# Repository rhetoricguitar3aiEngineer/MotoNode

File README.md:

# MotoNodeIQ

Motorcycle electronics for the 2003 Suzuki Katana 600: CAN body-electronics boards, an
ignition controller, and an Android telemetry app. Reorganized 2026-10-10. This repo mirrors the
`MotoNodeIQ` folder on the design PC, which is the source of truth for the current hardware.

**Status: designed and checked in software (KiCad 10 ERC/DRC clean), nothing built or bench-tested.**

| Folder | What | Status |
|---|---|---|
| [`Boards/`](Boards/) | **Front and rear CAN modules**: `front/`, `rear/` (Rev B, 76.2 x 50.8 mm) plus `generator/` that rebuilds them (`generator/build.py <board>`). `hub/` is superseded: the hub is now the ignition board (see below). [`Boards/README.md`](Boards/README.md) has the details and the "before you order" list. | Live (`hub/` superseded) |
| [`Boards/nodeiq_front_revG/`](Boards/nodeiq_front_revG/) | Hand-built Front Module Rev G, kept beside the generated `front/` | Reference |
| [`Ignition/RevE/`](Ignition/RevE/) | **The hub.** Ignition controller + hub on one board, Rev E: 4 TCI + 1 CDI, ESP32-S3, IMU/GPS/sensor inputs, 6-layer 100 x 70 mm, fully routed, DRC clean | Live |
| [`Telemetry/MotoNodeTelemetry/`](Telemetry/MotoNodeTelemetry/) | Android telemetry app + `esp32/` firmware (Gradle build output stripped; Android Studio regenerates it) | Live |
| [`Docs/`](Docs/) | Design brief, implementation plan, connector selection, source audit, board status (from the Codex NodeIQ work), plus [`OVERVIEW.md`](Docs/OVERVIEW.md) | Reference |
| [`Archive/`](Archive/) | Superseded material, see [`Archive/README.md`](Archive/README.md) | Archived |

`_Keys/keyMN1` (the Android app-signing keystore) lives beside these folders on the PC and is
**deliberately not in this repo**. It is irreplaceable: back it up off the PC, and never commit it.
`.gitignore` blocks `_Keys/` and keystore files.

## Not yet in the repo

Docs, BOMs, check reports and the telemetry source are here. The KiCad design files (`.kicad_*`,
libraries, `fab/`) and the Python generators (`Boards/generator/`, `Ignition/RevE/pcb_layout/`,
`Ignition/RevE/spice/`) still need to be pushed from the PC. See
[`Docs/FILES_TO_ADD.md`](Docs/FILES_TO_ADD.md).

## Google Drive

My Drive/**MotoNodeIQ** (<https://drive.google.com/drive/folders/14qOt1xsgB9vhRgdrsN2DCoWwWa2cDshs>)
holds what is *not* here: NodeIQ Android app releases (App/), ESP32 firmware (Firmware/), marketing
images/videos (Marketing/), reports, AI handoffs, and pre-Rev-B hardware (Archive/). "My Computer (1)"
on Drive is a stale backup of the old PC layout.

## Decided

- **Ignition is part of the hub** (2026-10-10). The Rev E ignition board is the system hub, so the
  system is Ignition/hub + Front + Rear. `Boards/hub/` is superseded and kept only as a source of
  circuits to port. See [`Docs/OVERVIEW.md`](Docs/OVERVIEW.md) §4 for the hub functions Rev E
  doesn't have yet.

## Tools

- KiCad 10.0.6. Its Python (`D:\Documents\bin\python.exe` on the PC) is needed by `pcbgen.py` / `pcbfinish.py`.
- Router and other generator scripts use system Python (numpy, scipy, shapely, PIL).
- ngspice 42 for `Ignition/RevE/spice/`.
- Android Studio (Gradle 9.5, JDK 17) and the Arduino ESP32 core for `Telemetry/`.

## Safety

The ignition board generates ~350 V on the CDI bus. Treat an assembled board as live and lethal, and
bench-test with current-limited supplies before it goes near a bike.

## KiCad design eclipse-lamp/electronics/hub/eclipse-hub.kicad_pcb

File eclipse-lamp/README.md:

# ECLIPSE Tree: a cedar elm made of light

ECLIPSE Tree is a desk lamp in the form of an old cedar elm (*Ulmus crassifolia*). In
daylight it reads as a small tree in leaf; switched on, it fills with light:

* **Grown, not drawn.** The crown is grown by space colonisation: buds compete for space in
  a rounded crown, so the wood forks where the space divides and tapers continuously (pipe
  model) from a 77 mm trunk through three leaders to **1,174 twigs**.
* **Leaves.** 40 flexible-circuit sprays carry **800 LED leaves** (0402) among **21,770
  leaves of light-diffusing film**, so the foliage glows green-gold around every light.
* **Trunk.** The trunk, its fork and its buttress roots are a thin bronze shell around a
  light-diffusing acrylic light-guide tube. Light travels down the tube and leaks out
  wherever the bark is split, so the trunk glows through its furrows.
* **Seeds.** End-glow optical fibres light **567 diffusing samaras** (cedar-elm seeds) among
  the twigs.

Warm and cool light is interleaved everywhere, so the whole tree can be mixed from candle
glow to daylight, dimmed to embers, or left with only its roots glowing.

| | |
|---|---|
|  |  |
|  |  |
|  |  |
|  |  |

## Four light paths, one driver per colour channel

```
                     ┌─ 2 top LEDs ──► fibre ferrule ──► 4 bundles × ~142 end-glow fibres ──► 567 glowing samaras
 HUB light engine  ──┤
 (in the trunk fork) └─ 2 bottom LEDs ─► trunk PMMA light-guide tube ──► TIR + extraction ──► glowing bark furrows
        │                                                                                    and buttress roots
        └─ then 10 LED sprigs in series ──► 20 × 0402 leaves each ──► 800 LED leaves ──► glowing leaf film

 CORE board (base): USB-C PD 9 V → 4 × TPS61165 constant-current boost @ 100 mA (W1 C1 W2 C2)
                    ATtiny1616 touch wheel, colour mix, + 8 LEDs → opal root-glow band (night light)
```

Each colour channel is **one series string of 11 elements** (≈31.5 V, inside the 38 V OVP):
first the hub's 4-LED light-engine group, then 10 sprigs. So all four optical systems dim
and colour-shift together from the same four drivers. The core board circuit is unchanged
from the previous revision, and only 10 wires run down the trunk.

## Key specs

| | |
|---|---|
| Size | ≈435 mm tall, crown ≈370 × 360 mm, on a Ø150 mm base |
| Tree | Space-colonisation grown cedar elm: 77 mm trunk (cast bronze shell + PMMA light-guide tube), 7 buttress roots, 3 leaders, 1,174 branches and twigs, 21,770 film leaves (seeded, reproducible) |
| Light sources | 800 × 0402 LED leaves + 16 × 2835 light-engine LEDs (8 → fibres, 8 → trunk core) + 8 × 2835 root glow |
| Optics | PMMA light-guide trunk with fissure extraction · light-diffusing leaf film lit by the LED leaves · 567 × 0.5 mm end-glow PMMA fibres in 4 bundles · 567 diffusing-epoxy samaras · opal root band |
| Light | 12.6 W max LED power (firmware cap ≈8.5 W), ≈600 lm total (estimated), 2700-6500 K, flicker-free |
| Mass / stability | ≈4.1 kg, centre of gravity 8.5 mm from the base centre (66 mm inside the base edge) |
| Power / controls | USB-C PD 9 V (18 W+ charger), capacitive wheel through 3 mm glass |

## What's in this folder

```
eclipse-lamp/
├── mechanical/   tree_gen.py (space-colonisation cedar elm: trunk, fork, roots, wood, sprigs, samaras, foliage),
│                 eclipse_cad.py (CadQuery, mass/CoG), wiring_map.py, out/ (STEP/STL, big STEPs zipped,
│                 foliage.stl leaf-cutting file, parts.json)
├── electronics/
│   ├── core/     KiCad 9: base board (power, 4 drivers, touch MCU, root glow), unchanged circuit
│   ├── hub/      KiCad 9: Ø56 two-sided light engine in the trunk fork (16 LEDs) + 40 sprig lands + chaining + NTC
│   ├── sprig/    KiCad 9: polyimide flex cedar-elm spray, 20 × 0402 LED leaves (×40 per lamp)
│   ├── lib/      custom footprints + 3D models
│   └── tools/    generators: schematics (wire router), PCBs, layouts, netlist checks, fab export
├── bom/          eclipse_bom.csv, BOM.md (≈$147 material at 1k units, estimates)
├── renders/      Cycles renders + KiCad board renders, render_blender.py
└── docs/         DESIGN.md (design notes, optics, calculations), WIRING.md (sprig map)
```

## Verification

Every schematic draws every signal connection as a visible wire. There are no net labels,
and power uses power symbols only (see `/CLAUDE.md`).

| Check | Core | Hub | Sprig |
|---|---|---|---|
| ERC | 0 / 0 | 0 / 0 | 0 / 0 |
| DRC | 0 violations | 0 violations | 0 violations |
| Unrouted | 0 | 0 | 0 |
| Schematic ↔ PCB parity | 0 issues | 0 issues | 0 issues |
| Netlist vs design intent | 0 mismatches | 0 mismatches | 0 mismatches |

## Rebuild everything

Requires KiCad 9 (`kicad-cli` + `pcbnew` Python), CadQuery 2.x, numpy, scipy, shapely, Freerouting 1.9
(core board only, Java 21 + `xvfb-run`) and the `bpy` 5.x module for renders.

```sh
cd electronics/tools
python3 make_footprints.py && python3 make_3d_models.py
for b in core hub sprig; do
  python3 design_$b.py ../$b/eclipse-$b.kicad_sch
  (cd ../$b && kicad-cli sch export netlist --format kicadsexpr -o eclipse-$b.net eclipse-$b.kicad_sch)
  python3 verify_netlist.py design_$b ../$b/eclipse-$b.net
done
python3 pcb_hub.py && python3 pcb_sprig.py   # parametric layouts
./route_core.sh                             # core: placement → Freerouting → pours → DRC
./export_fab.sh                             # gerbers, drill, P&P, PDFs, STEP/GLB, reports
cd ../../mechanical && python3 eclipse_cad.py && python3 wiring_map.py
cd ../bom && python3 make_bom.py
cd ../renders && python3 render_blender.py hero   # hero | trunk | leaves | night | studio | cool | detail
```

See [docs/DESIGN.md](docs/DESIGN.md) for the optics, the calculations and the open items.

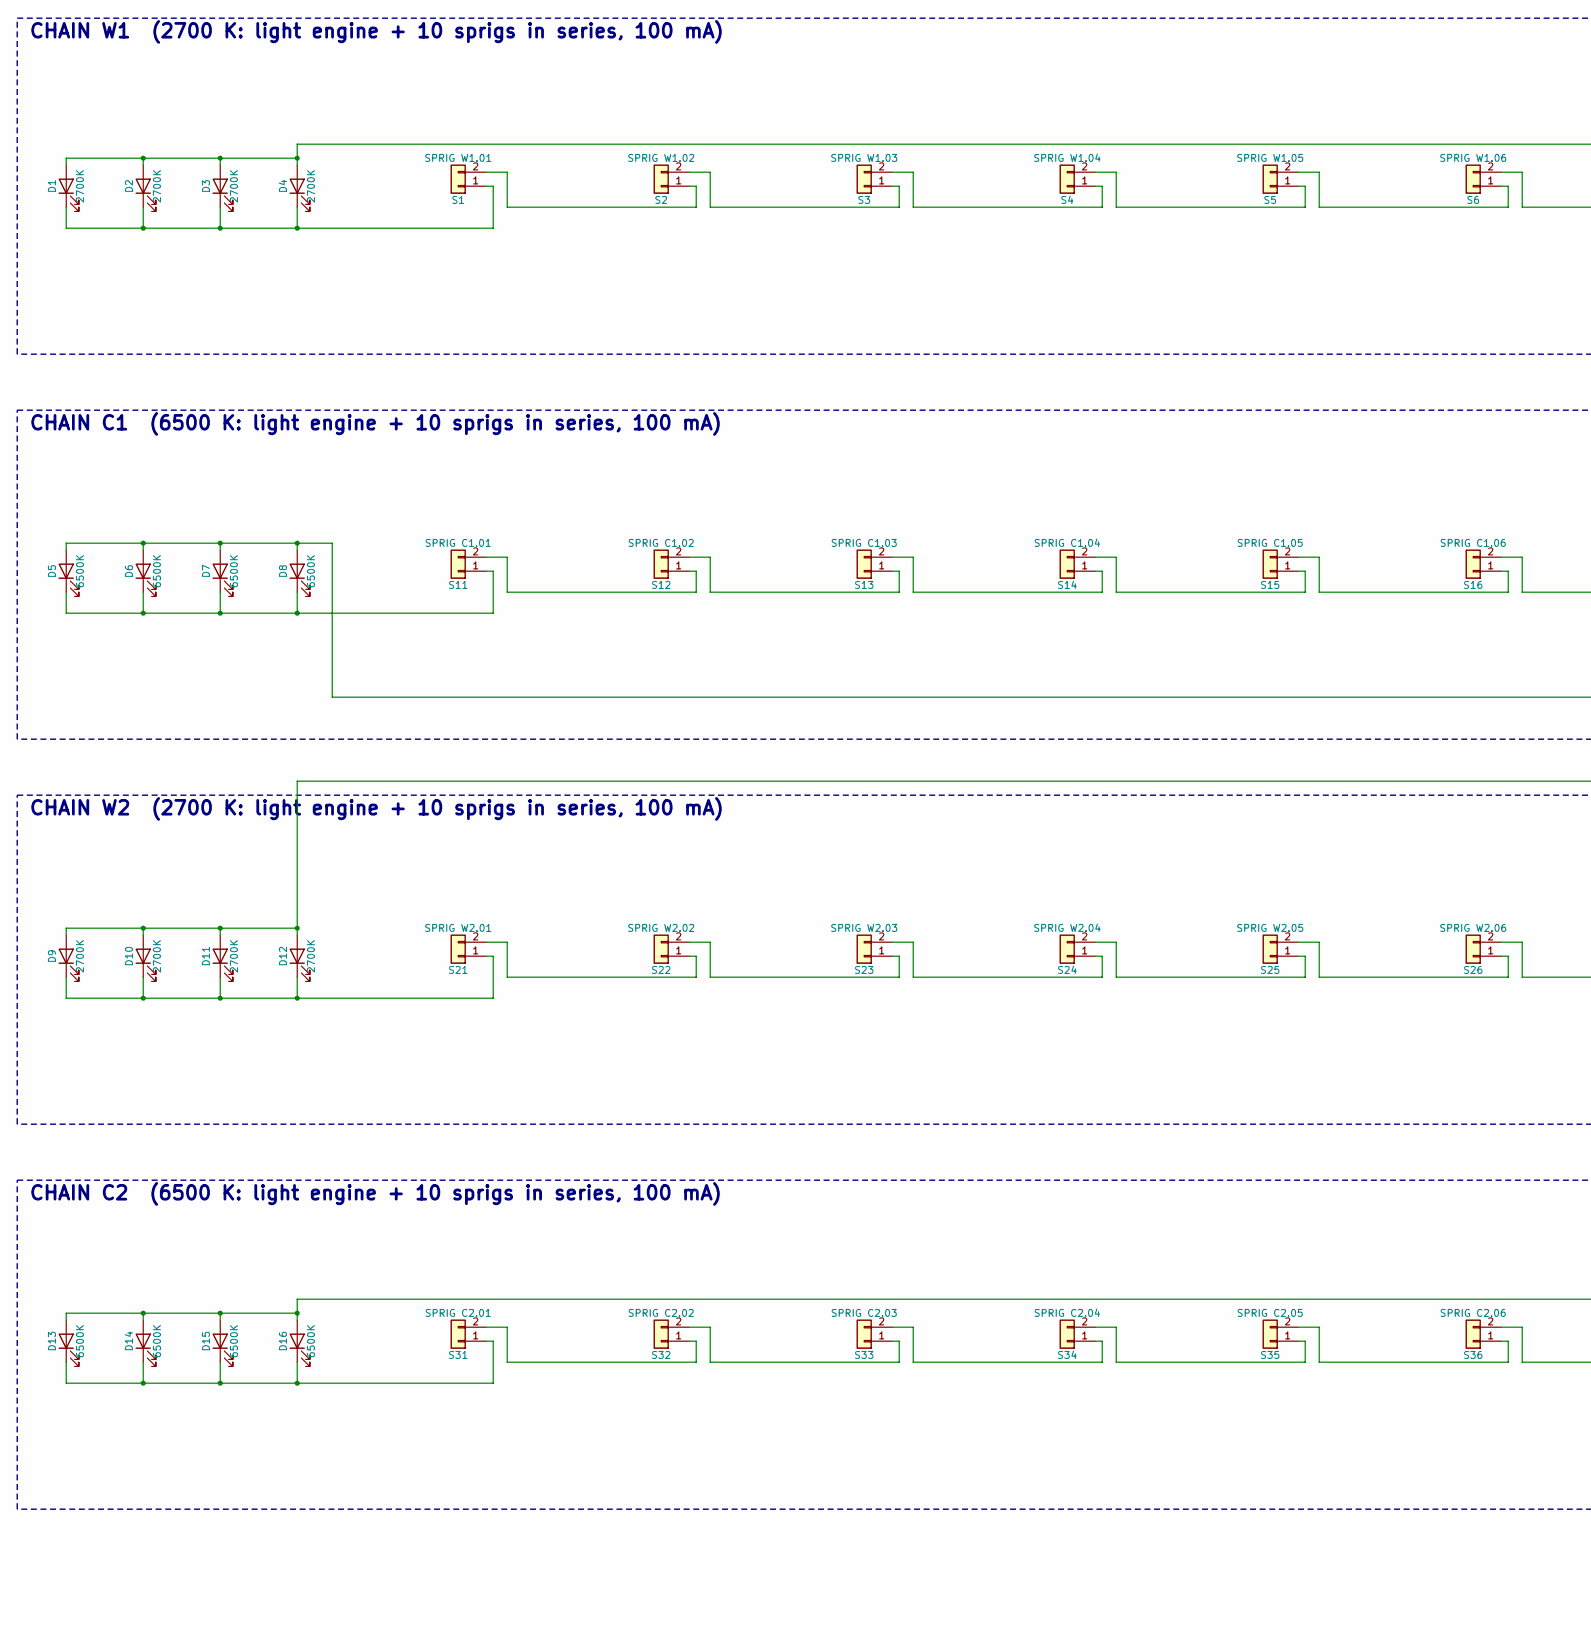
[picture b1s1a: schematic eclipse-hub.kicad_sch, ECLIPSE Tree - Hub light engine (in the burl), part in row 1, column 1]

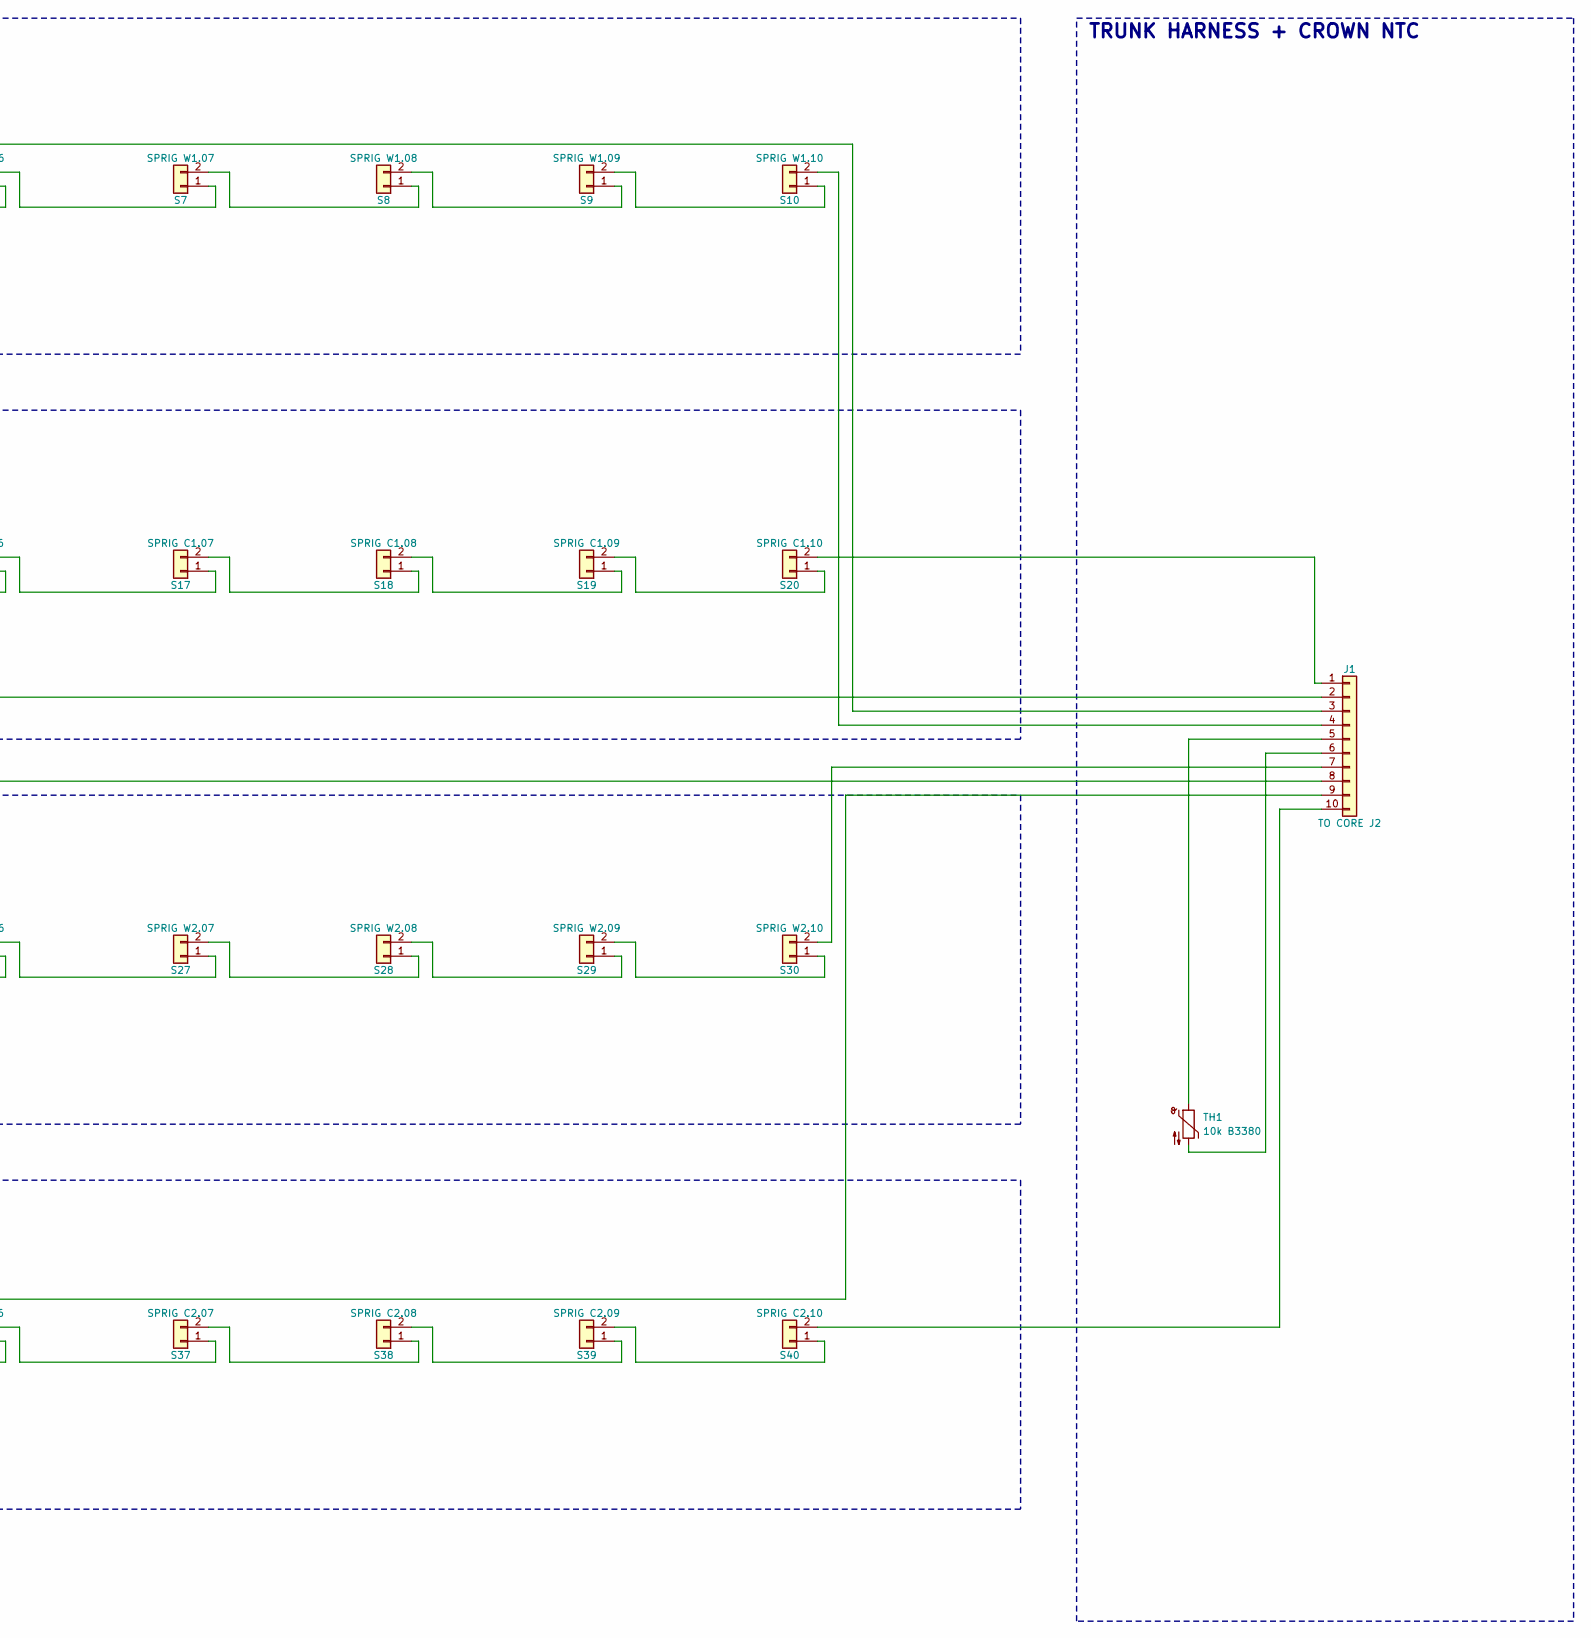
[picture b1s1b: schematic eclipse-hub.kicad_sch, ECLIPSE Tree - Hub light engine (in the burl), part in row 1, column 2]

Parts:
D1, D2, D3, D4, D9, D10, D11, D12: 2700K; LED_PLCC_2835; MPN LM281B+ 2700K
D5, D6, D7, D8, D13, D14, D15, D16: 6500K; LED_PLCC_2835; MPN LM281B+ 6500K
J1: TO CORE J2; HubTrunkPads; MPN wire lands
S1: SPRIG W1.01; HubSprigPads; MPN wire lands
S2: SPRIG W1.02; HubSprigPads; MPN wire lands
S3: SPRIG W1.03; HubSprigPads; MPN wire lands
S4: SPRIG W1.04; HubSprigPads; MPN wire lands
S5: SPRIG W1.05; HubSprigPads; MPN wire lands
S6: SPRIG W1.06; HubSprigPads; MPN wire lands
S7: SPRIG W1.07; HubSprigPads; MPN wire lands
S8: SPRIG W1.08; HubSprigPads; MPN wire lands
S9: SPRIG W1.09; HubSprigPads; MPN wire lands
S10: SPRIG W1.10; HubSprigPads; MPN wire lands
S11: SPRIG C1.01; HubSprigPads; MPN wire lands
S12: SPRIG C1.02; HubSprigPads; MPN wire lands
S13: SPRIG C1.03; HubSprigPads; MPN wire lands
S14: SPRIG C1.04; HubSprigPads; MPN wire lands
S15: SPRIG C1.05; HubSprigPads; MPN wire lands
S16: SPRIG C1.06; HubSprigPads; MPN wire lands
S17: SPRIG C1.07; HubSprigPads; MPN wire lands
S18: SPRIG C1.08; HubSprigPads; MPN wire lands
S19: SPRIG C1.09; HubSprigPads; MPN wire lands
S20: SPRIG C1.10; HubSprigPads; MPN wire lands
S21: SPRIG W2.01; HubSprigPads; MPN wire lands
S22: SPRIG W2.02; HubSprigPads; MPN wire lands
S23: SPRIG W2.03; HubSprigPads; MPN wire lands
S24: SPRIG W2.04; HubSprigPads; MPN wire lands
S25: SPRIG W2.05; HubSprigPads; MPN wire lands
S26: SPRIG W2.06; HubSprigPads; MPN wire lands
S27: SPRIG W2.07; HubSprigPads; MPN wire lands
S28: SPRIG W2.08; HubSprigPads; MPN wire lands
S29: SPRIG W2.09; HubSprigPads; MPN wire lands
S30: SPRIG W2.10; HubSprigPads; MPN wire lands
S31: SPRIG C2.01; HubSprigPads; MPN wire lands
S32: SPRIG C2.02; HubSprigPads; MPN wire lands
S33: SPRIG C2.03; HubSprigPads; MPN wire lands
S34: SPRIG C2.04; HubSprigPads; MPN wire lands
S35: SPRIG C2.05; HubSprigPads; MPN wire lands
S36: SPRIG C2.06; HubSprigPads; MPN wire lands
S37: SPRIG C2.07; HubSprigPads; MPN wire lands
S38: SPRIG C2.08; HubSprigPads; MPN wire lands
S39: SPRIG C2.09; HubSprigPads; MPN wire lands
S40: SPRIG C2.10; HubSprigPads; MPN wire lands
TH1: 10k B3380; R_0603_1608Metric; MPN NCP18XH103F03RB

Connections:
unnamed: D1.2 (A), D2.2 (A), D3.2 (A), D4.2 (A), J1.3
unnamed: D1.1 (K), D2.1 (K), D3.1 (K), D4.1 (K), S1.1
unnamed: D5.2 (A), D6.2 (A), D7.2 (A), D8.2 (A), J1.2
unnamed: D5.1 (K), D6.1 (K), D7.1 (K), D8.1 (K), S11.1
unnamed: D9.2 (A), D10.2 (A), D11.2 (A), D12.2 (A), J1.8
unnamed: D9.1 (K), D10.1 (K), D11.1 (K), D12.1 (K), S21.1
unnamed: D13.2 (A), D14.2 (A), D15.2 (A), D16.2 (A), J1.9
unnamed: D13.1 (K), D14.1 (K), D15.1 (K), D16.1 (K), S31.1
unnamed: J1.1, S20.2
unnamed: J1.4, S10.2
unnamed: J1.5, TH1.1
unnamed: J1.6, TH1.2
unnamed: J1.7, S30.2
unnamed: J1.10, S40.2
unnamed: S1.2, S2.1
unnamed: S2.2, S3.1
unnamed: S3.2, S4.1
unnamed: S4.2, S5.1
unnamed: S5.2, S6.1
unnamed: S6.2, S7.1
unnamed: S7.2, S8.1
unnamed: S8.2, S9.1
unnamed: S9.2, S10.1
unnamed: S11.2, S12.1
unnamed: S12.2, S13.1
unnamed: S13.2, S14.1
unnamed: S14.2, S15.1
unnamed: S15.2, S16.1
unnamed: S16.2, S17.1
unnamed: S17.2, S18.1
unnamed: S18.2, S19.1
unnamed: S19.2, S20.1
unnamed: S21.2, S22.1
unnamed: S22.2, S23.1
unnamed: S23.2, S24.1
unnamed: S24.2, S25.1
unnamed: S25.2, S26.1
unnamed: S26.2, S27.1
unnamed: S27.2, S28.1
unnamed: S28.2, S29.1
unnamed: S29.2, S30.1
unnamed: S31.2, S32.1
unnamed: S32.2, S33.1
unnamed: S33.2, S34.1
unnamed: S34.2, S35.1
unnamed: S35.2, S36.1
unnamed: S36.2, S37.1
unnamed: S37.2, S38.1
unnamed: S38.2, S39.1
unnamed: S39.2, S40.1

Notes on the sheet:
CHAIN W1 (2700 K: light engine + 10 sprigs in series, 100 mA)
CHAIN C1 (6500 K: light engine + 10 sprigs in series, 100 mA)
CHAIN W2 (2700 K: light engine + 10 sprigs in series, 100 mA)
CHAIN C2 (6500 K: light engine + 10 sprigs in series, 100 mA)
TRUNK HARNESS + CROWN NTC

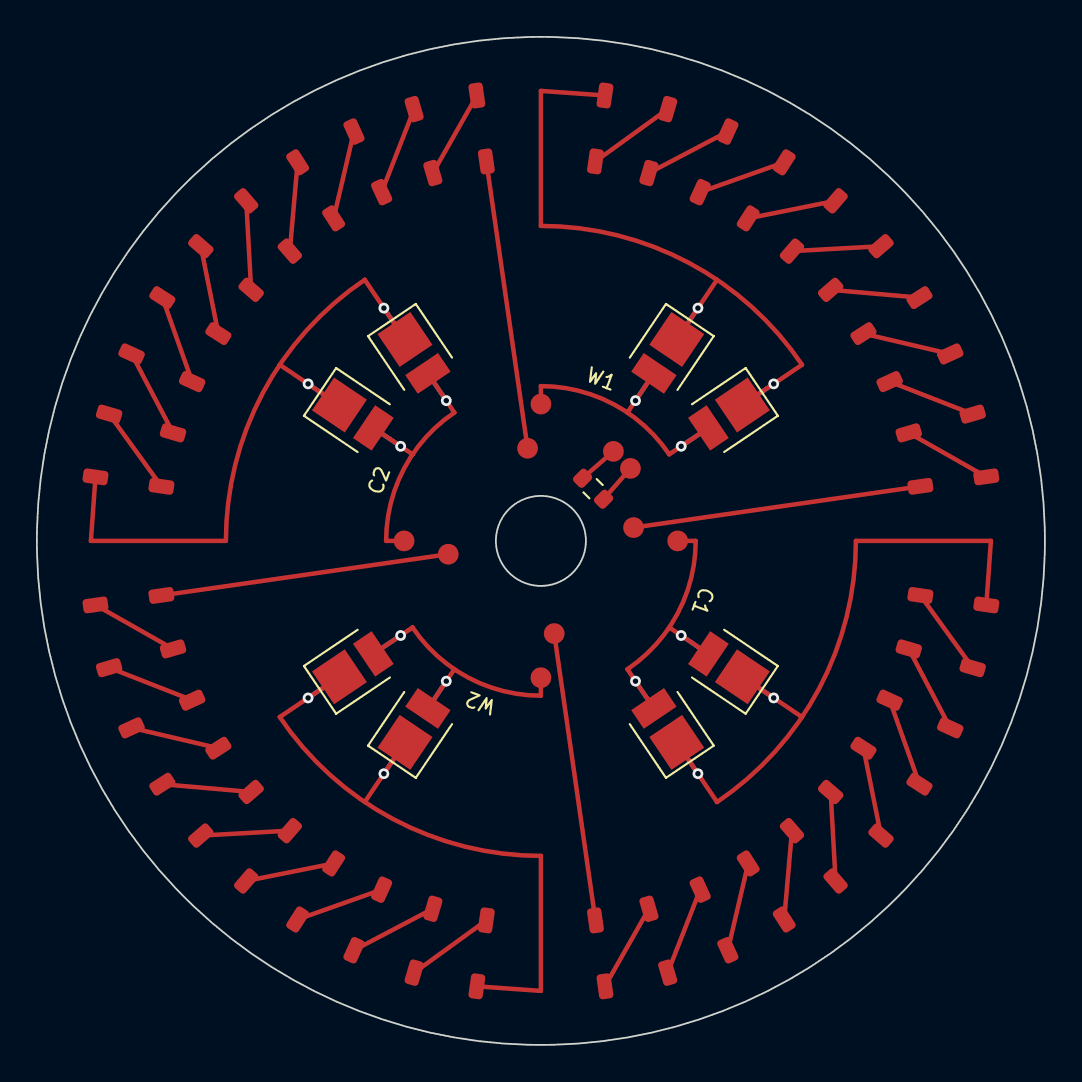
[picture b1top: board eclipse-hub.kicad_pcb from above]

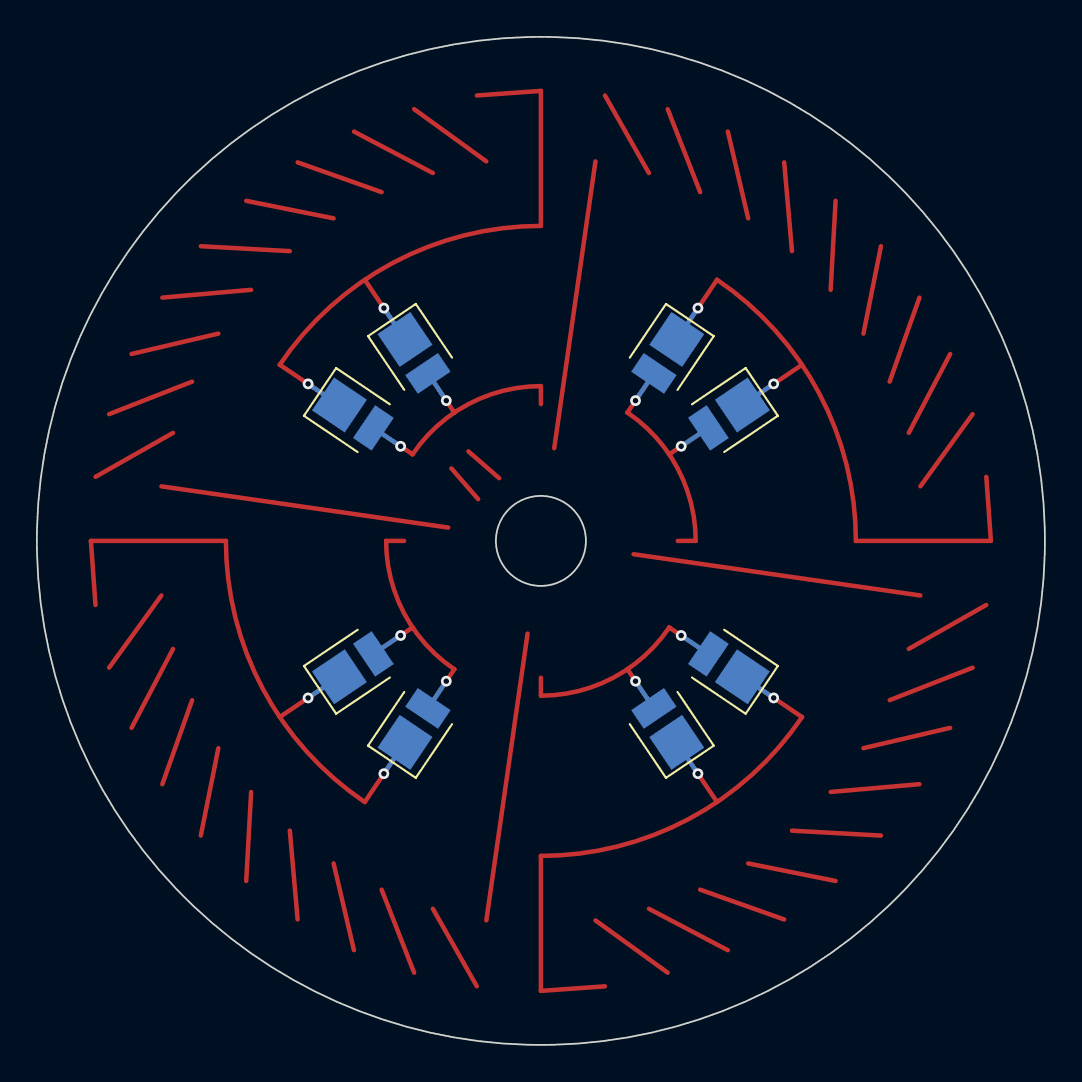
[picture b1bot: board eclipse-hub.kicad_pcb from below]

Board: 2 copper layers, 56.0 x 56.0 mm, 58 parts (8 on the bottom side), 50 nets.

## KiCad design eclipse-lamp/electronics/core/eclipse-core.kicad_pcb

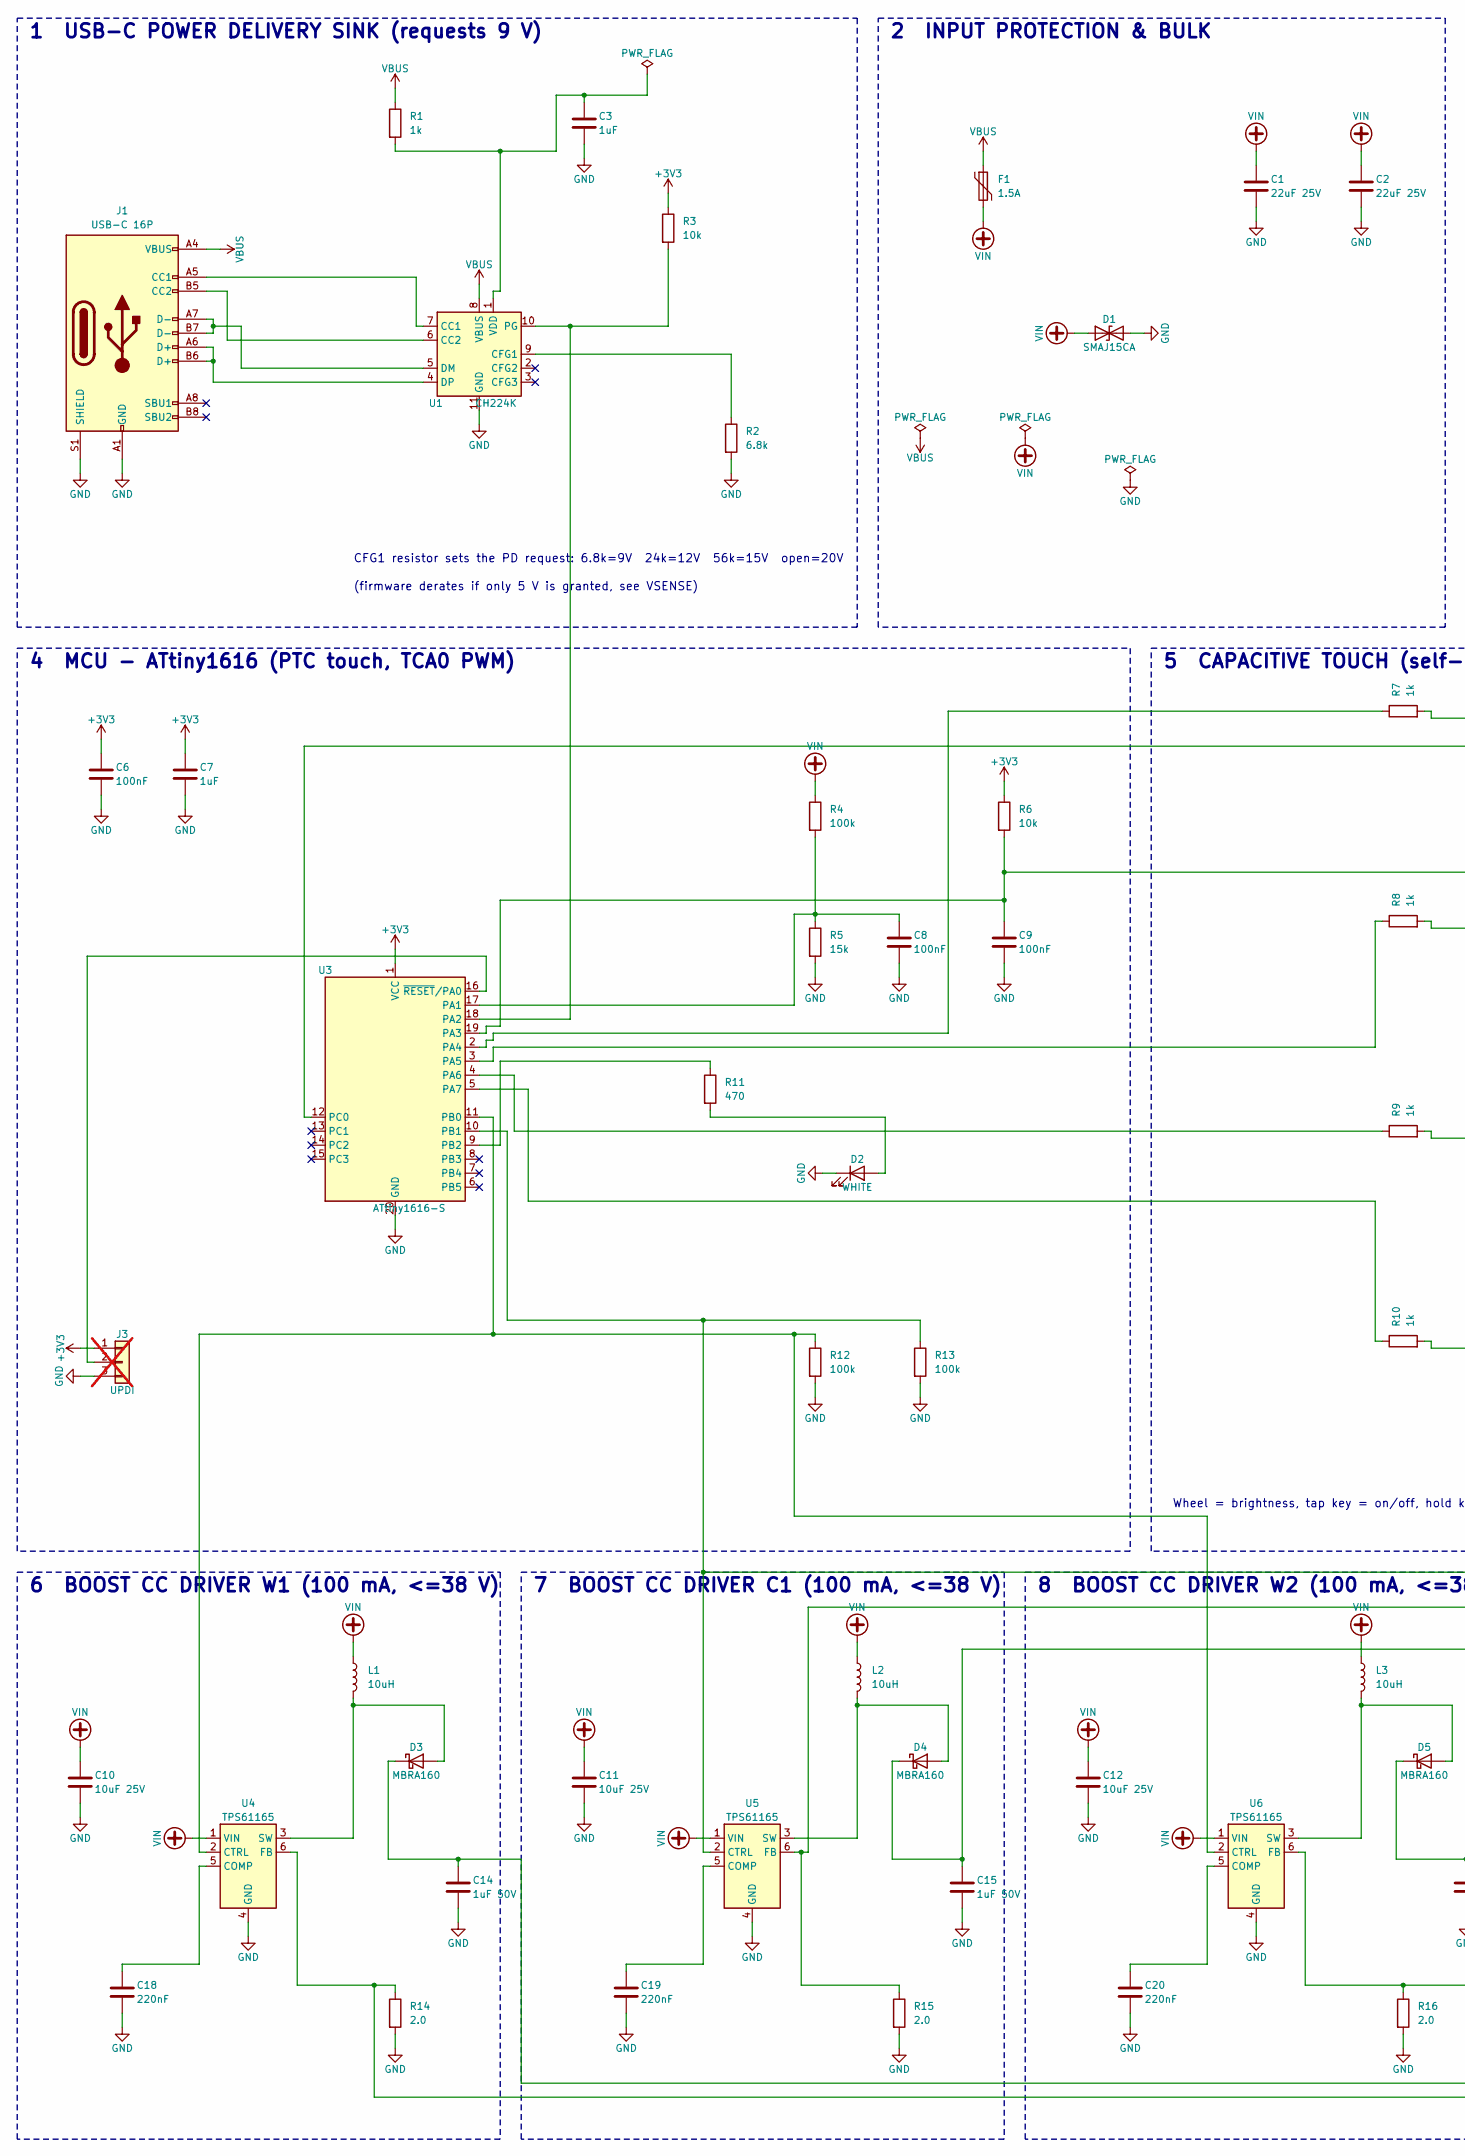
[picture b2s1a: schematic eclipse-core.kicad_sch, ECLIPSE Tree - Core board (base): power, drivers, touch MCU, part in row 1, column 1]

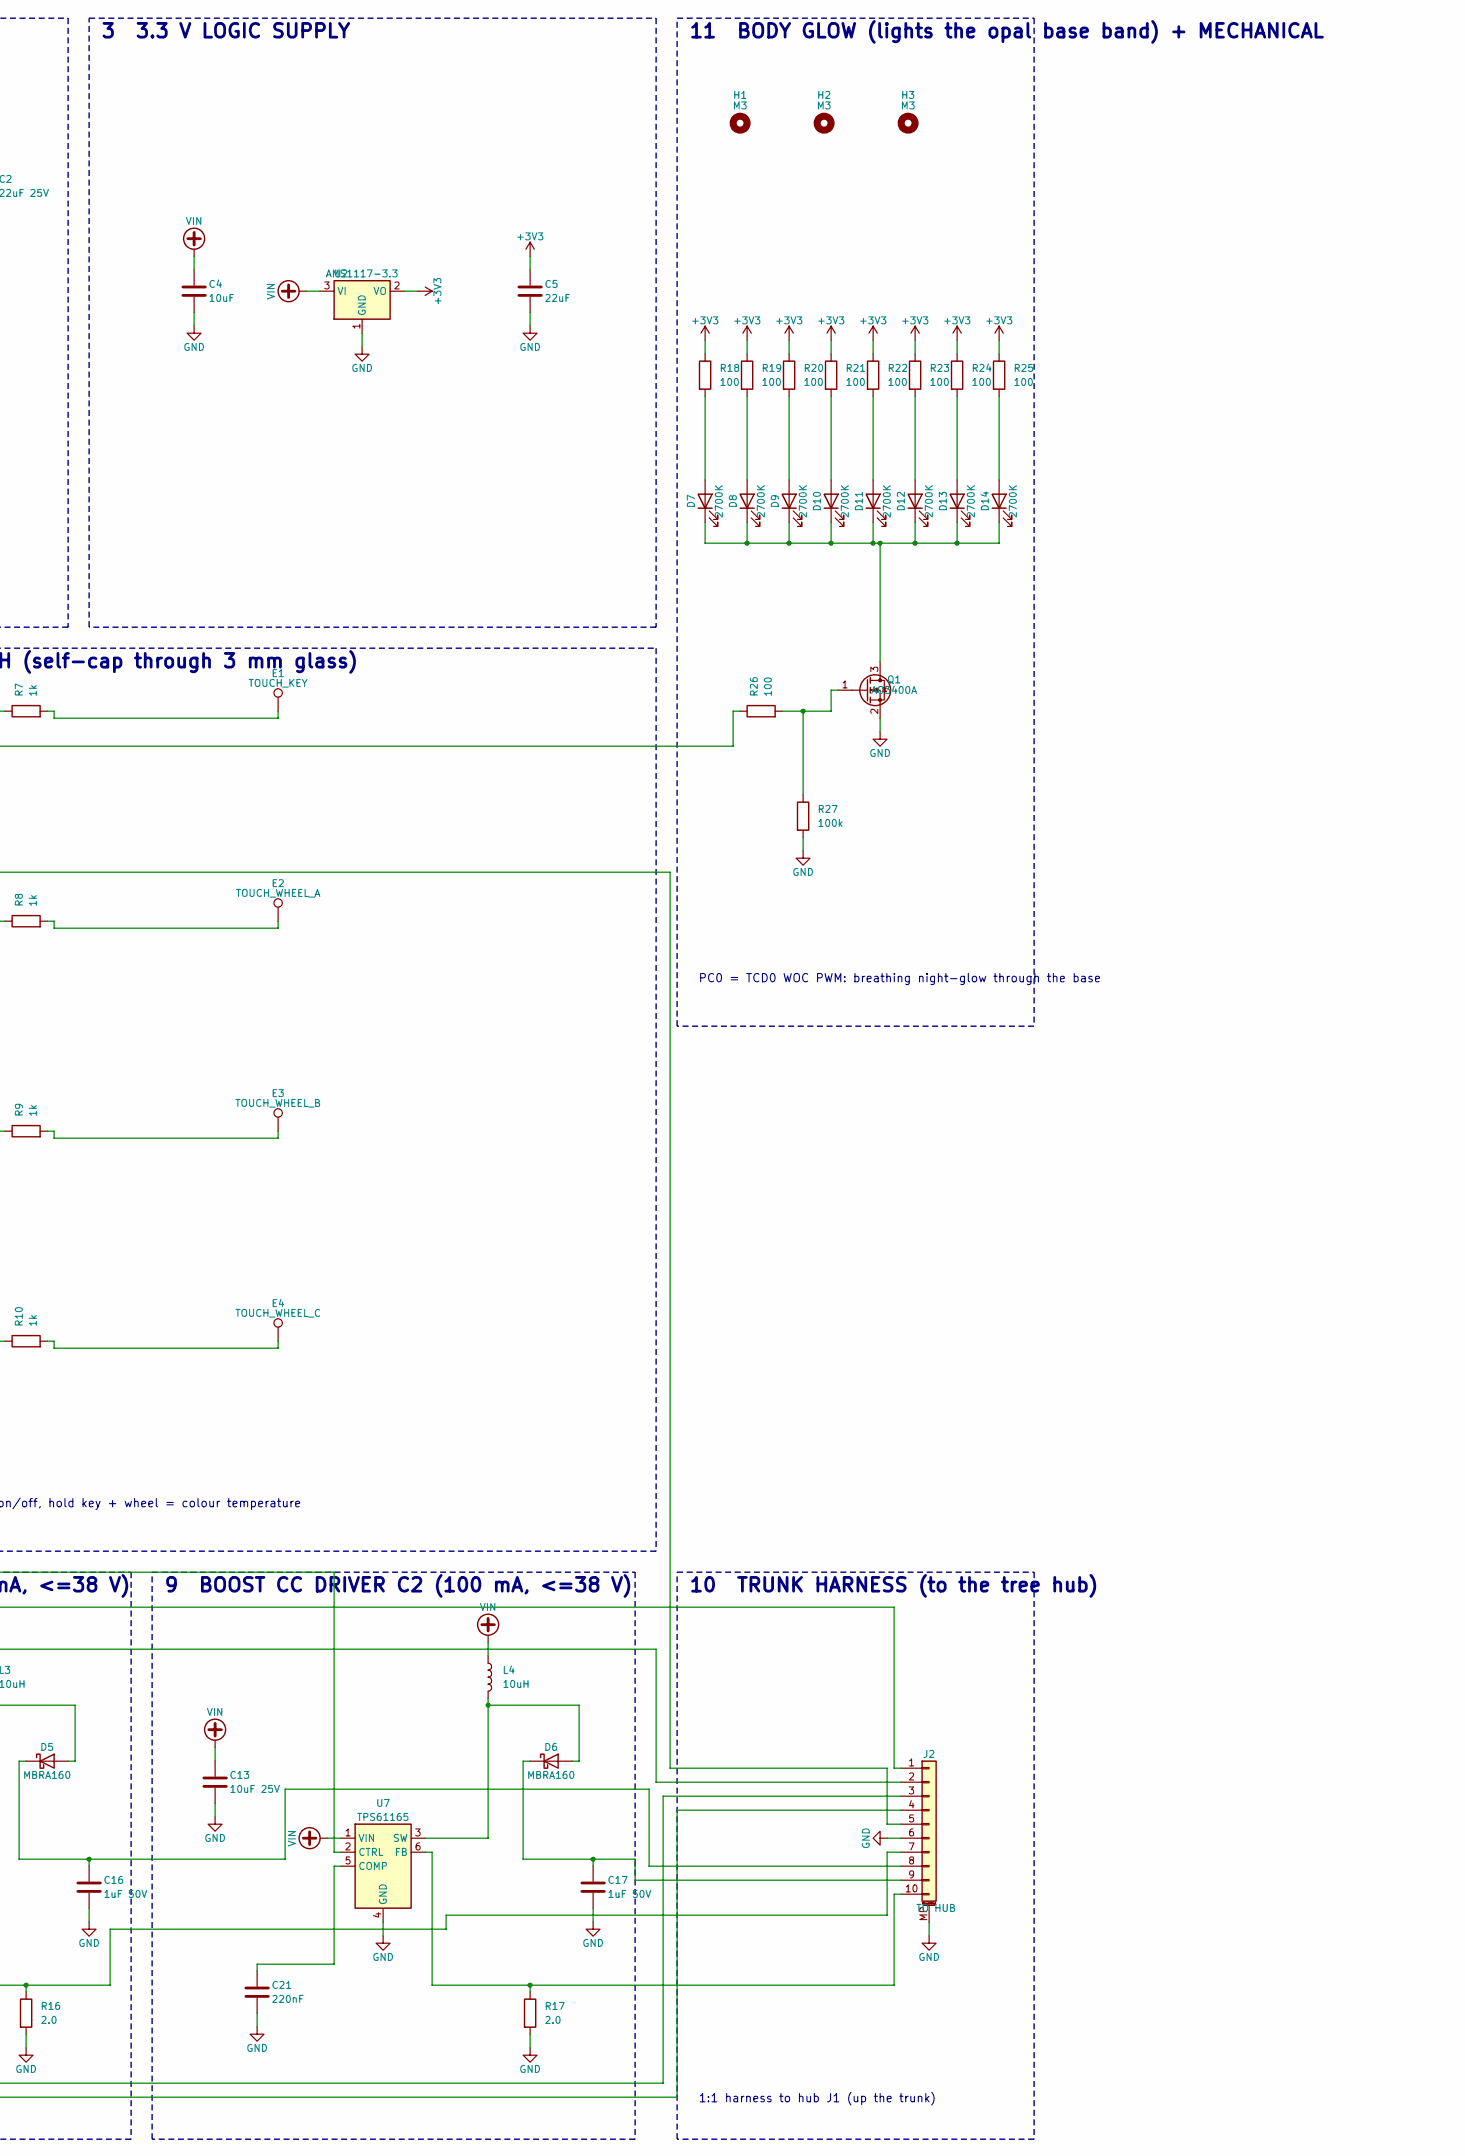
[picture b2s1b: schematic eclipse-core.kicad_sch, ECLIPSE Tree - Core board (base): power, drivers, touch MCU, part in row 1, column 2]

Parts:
C1, C2: 22uF 25V; C_1206_3216Metric; MPN GRM31CR61E226KE15L
C3, C7: 1uF; C_0603_1608Metric; MPN GRM188R61E105KA12D
C4: 10uF; C_0805_2012Metric; MPN CL21A106KAYNNNE
C5: 22uF; C_0805_2012Metric; MPN CL21A226MAQNNNE
C6, C8, C9: 100nF; C_0603_1608Metric; MPN GRM188R71H104KA93D
C10, C11, C12, C13: 10uF 25V; C_0805_2012Metric; MPN CL21A106KAYNNNE
C14, C15, C16, C17: 1uF 50V; C_1206_3216Metric; MPN GRM31MR71H105KA88L
C18, C19, C20, C21: 220nF; C_0603_1608Metric; MPN GRM188R71E224KA88D
D1: SMAJ15CA; D_SMA; MPN SMAJ15CA
D2: WHITE; LED_0603_1608Metric; MPN LTW-C191TS5
D3, D4, D5, D6: MBRA160; D_SMA; MPN MBRA160T3G
D7, D8, D9, D10, D11, D12, D13, D14: 2700K; LED_PLCC_2835; MPN LM281B+ 2700K
E1: TOUCH_KEY; TouchKey_D14; MPN PCB copper electrode
E2: TOUCH_WHEEL_A; TouchWheel_Seg120; MPN PCB copper electrode
E3: TOUCH_WHEEL_B; TouchWheel_Seg120; MPN PCB copper electrode
E4: TOUCH_WHEEL_C; TouchWheel_Seg120; MPN PCB copper electrode
F1: 1.5A; Fuse_1812_4532Metric; MPN MF-MSMF150/24X-2
H1, H2, H3: M3; MountingHole_3.2mm_M3
J1: USB-C 16P; USB_C_Receptacle_HRO_TYPE-C-31-M-12; MPN TYPE-C-31-M-12; LCSC C165948
J2: TO HUB; JST_PH_S10B-PH-SM4-TB_1x10-1MP_P2.00mm_Horizontal; MPN S10B-PH-SM4-TB
J3: UPDI; PinHeader_1x03_P2.54mm_Vertical; MPN DNP (pogo pads); not fitted
L1, L2, L3, L4: 10uH; L_Bourns-SRN4018; MPN SRN4018-100M
Q1: AO3400A; SOT-23; MPN AO3400A
R1, R7, R8, R9, R10: 1k; R_0603_1608Metric; MPN RC0603FR-071KL
R2: 6.8k; R_0603_1608Metric; MPN RC0603FR-076K8L
R3, R6: 10k; R_0603_1608Metric; MPN RC0603FR-0710KL
R4, R12, R13, R27: 100k; R_0603_1608Metric; MPN RC0603FR-07100KL
R5: 15k; R_0603_1608Metric; MPN RC0603FR-0715KL
R11: 470; R_0603_1608Metric; MPN RC0603FR-07470RL
R14, R15, R16, R17: 2.0; R_0805_2012Metric; MPN RC0805FR-072RL
R18, R19, R20, R21, R22, R23, R24, R25, R26: 100; R_0603_1608Metric; MPN RC0603FR-07100RL
U1: CH224K; SSOP-10-1EP_3.9x4.9mm_P1mm_EP2.1x3.3mm; MPN CH224K; LCSC C970725
U2: AMS1117-3.3; SOT-223-3_TabPin2; MPN AMS1117-3.3; LCSC C6186
U3: ATtiny1616-S; SOIC-20W_7.5x12.8mm_P1.27mm; MPN ATTINY1616-SNR
U4, U5, U6, U7: TPS61165; SOT-23-6; MPN TPS61165DBVR

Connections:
+3V3: C5.1, C6.1, C7.1, J3.1, R3.1, R6.1, R18.1, R19.1, R20.1, R21.1, R22.1, R23.1, R24.1, R25.1, U2.2 (VO), U3.1 (VCC)
GND: C1.2, C2.2, C3.2, C4.2, C5.2, C6.2, C7.2, C8.2, C9.2, C10.2, C11.2, C12.2, C13.2, C14.2, C15.2, C16.2, C17.2, C18.2, C19.2, C20.2, C21.2, D1.2 (A2), D2.1 (K), J1.A1 (GND), J1.A12 (GND), J1.B1 (GND), J1.B12 (GND), J1.S1 (SHIELD), J2.6, J2.MP (MountPin), J3.3, Q1.2 (S), R2.2, R5.2, R12.2, R13.2, R14.2, R15.2, R16.2, R17.2, R27.2, U1.11 (GND), U2.1 (GND), U3.20 (GND), U4.4 (GND), U5.4 (GND), U6.4 (GND), U7.4 (GND)
unnamed: D2.2 (A), R11.2
unnamed: D3.2 (A), L1.2, U4.3 (SW)
unnamed: C14.1, D3.1 (K), J2.3
unnamed: D4.2 (A), L2.2, U5.3 (SW)
unnamed: C15.1, D4.1 (K), J2.2
unnamed: D5.2 (A), L3.2, U6.3 (SW)
unnamed: C16.1, D5.1 (K), J2.8
unnamed: D6.2 (A), L4.2, U7.3 (SW)
unnamed: C17.1, D6.1 (K), J2.9
unnamed: D7.2 (A), R18.2
unnamed: D8.2 (A), R19.2
unnamed: D9.2 (A), R20.2
unnamed: D10.2 (A), R21.2
unnamed: D7.1 (K), D8.1 (K), D9.1 (K), D10.1 (K), D11.1 (K), D12.1 (K), D13.1 (K), D14.1 (K), Q1.3 (D)
unnamed: D11.2 (A), R22.2
unnamed: D12.2 (A), R23.2
unnamed: D13.2 (A), R24.2
unnamed: D14.2 (A), R25.2
unnamed: E1.1, R7.2
unnamed: E2.1, R8.2
unnamed: E3.1, R9.2
unnamed: E4.1, R10.2
unnamed: J1.A5 (CC1), U1.7 (CC1)
unnamed: J1.B5 (CC2), U1.6 (CC2)
unnamed: J2.1, R15.1, U5.6 (FB)
unnamed: J2.4, R14.1, U4.6 (FB)
unnamed: C9.1, J2.5, R6.2, U3.19 (PA3)
unnamed: J2.7, R16.1, U6.6 (FB)
unnamed: J2.10, R17.1, U7.6 (FB)
unnamed: J3.2, U3.16 (~RESET/PA0)
unnamed: Q1.1 (G), R26.2, R27.1
unnamed: R2.1, U1.9 (CFG1)
unnamed: J1.A7 (D-), J1.B7 (D-), U1.5 (DM)
unnamed: J1.A6 (D+), J1.B6 (D+), U1.4 (DP)
unnamed: R3.2, U1.10 (PG), U3.18 (PA2)
unnamed: C3.1, R1.2, U1.1 (VDD)
unnamed: C8.1, R4.2, R5.1, U3.17 (PA1)
unnamed: R7.1, U3.2 (PA4)
unnamed: R8.1, U3.3 (PA5)
unnamed: R9.1, U3.4 (PA6)
unnamed: R10.1, U3.5 (PA7)
unnamed: R12.1, U3.11 (PB0), U4.2 (CTRL), U6.2 (CTRL)
unnamed: R13.1, U3.10 (PB1), U5.2 (CTRL), U7.2 (CTRL)
unnamed: R11.1, U3.9 (PB2)
unnamed: R26.1, U3.12 (PC0)
unnamed: C18.1, U4.5 (COMP)
unnamed: C19.1, U5.5 (COMP)
unnamed: C20.1, U6.5 (COMP)
unnamed: C21.1, U7.5 (COMP)
VBUS: F1.1, J1.A4 (VBUS), J1.A9 (VBUS), J1.B4 (VBUS), J1.B9 (VBUS), R1.1, U1.8 (VBUS)
VIN: C1.1, C2.1, C4.1, C10.1, C11.1, C12.1, C13.1, D1.1 (A1), F1.2, L1.1, L2.1, L3.1, L4.1, R4.1, U2.3 (VI), U4.1 (VIN), U5.1 (VIN), U6.1 (VIN), U7.1 (VIN)

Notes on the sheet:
1 USB-C POWER DELIVERY SINK (requests 9 V)
CFG1 resistor sets the PD request: 6.8k=9V 24k=12V 56k=15V open=20V
(firmware derates if only 5 V is granted, see VSENSE)
2 INPUT PROTECTION & BULK
3 3.3 V LOGIC SUPPLY
4 MCU - ATtiny1616 (PTC touch, TCA0 PWM)
5 CAPACITIVE TOUCH (self-cap through 3 mm glass)
Wheel = brightness, tap key = on/off, hold key + wheel = colour temperature
6 BOOST CC DRIVER W1 (100 mA, <=38 V)
7 BOOST CC DRIVER C1 (100 mA, <=38 V)
8 BOOST CC DRIVER W2 (100 mA, <=38 V)
9 BOOST CC DRIVER C2 (100 mA, <=38 V)
11 BODY GLOW (lights the opal base band) + MECHANICAL
PC0 = TCD0 WOC PWM: breathing night-glow through the base
10 TRUNK HARNESS (to the tree hub)
1:1 harness to hub J1 (up the trunk)
